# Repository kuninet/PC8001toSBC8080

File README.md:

# PC-8001 50Pバスと、SBC8080バスの変換

## 概要

* PC-8001外部CPUバスをSBC8080バスへ変換するボード

## 必要な電子部品等...

* 74LS32 OR GATE
* 74LS05 NOT (OPENドレイン)

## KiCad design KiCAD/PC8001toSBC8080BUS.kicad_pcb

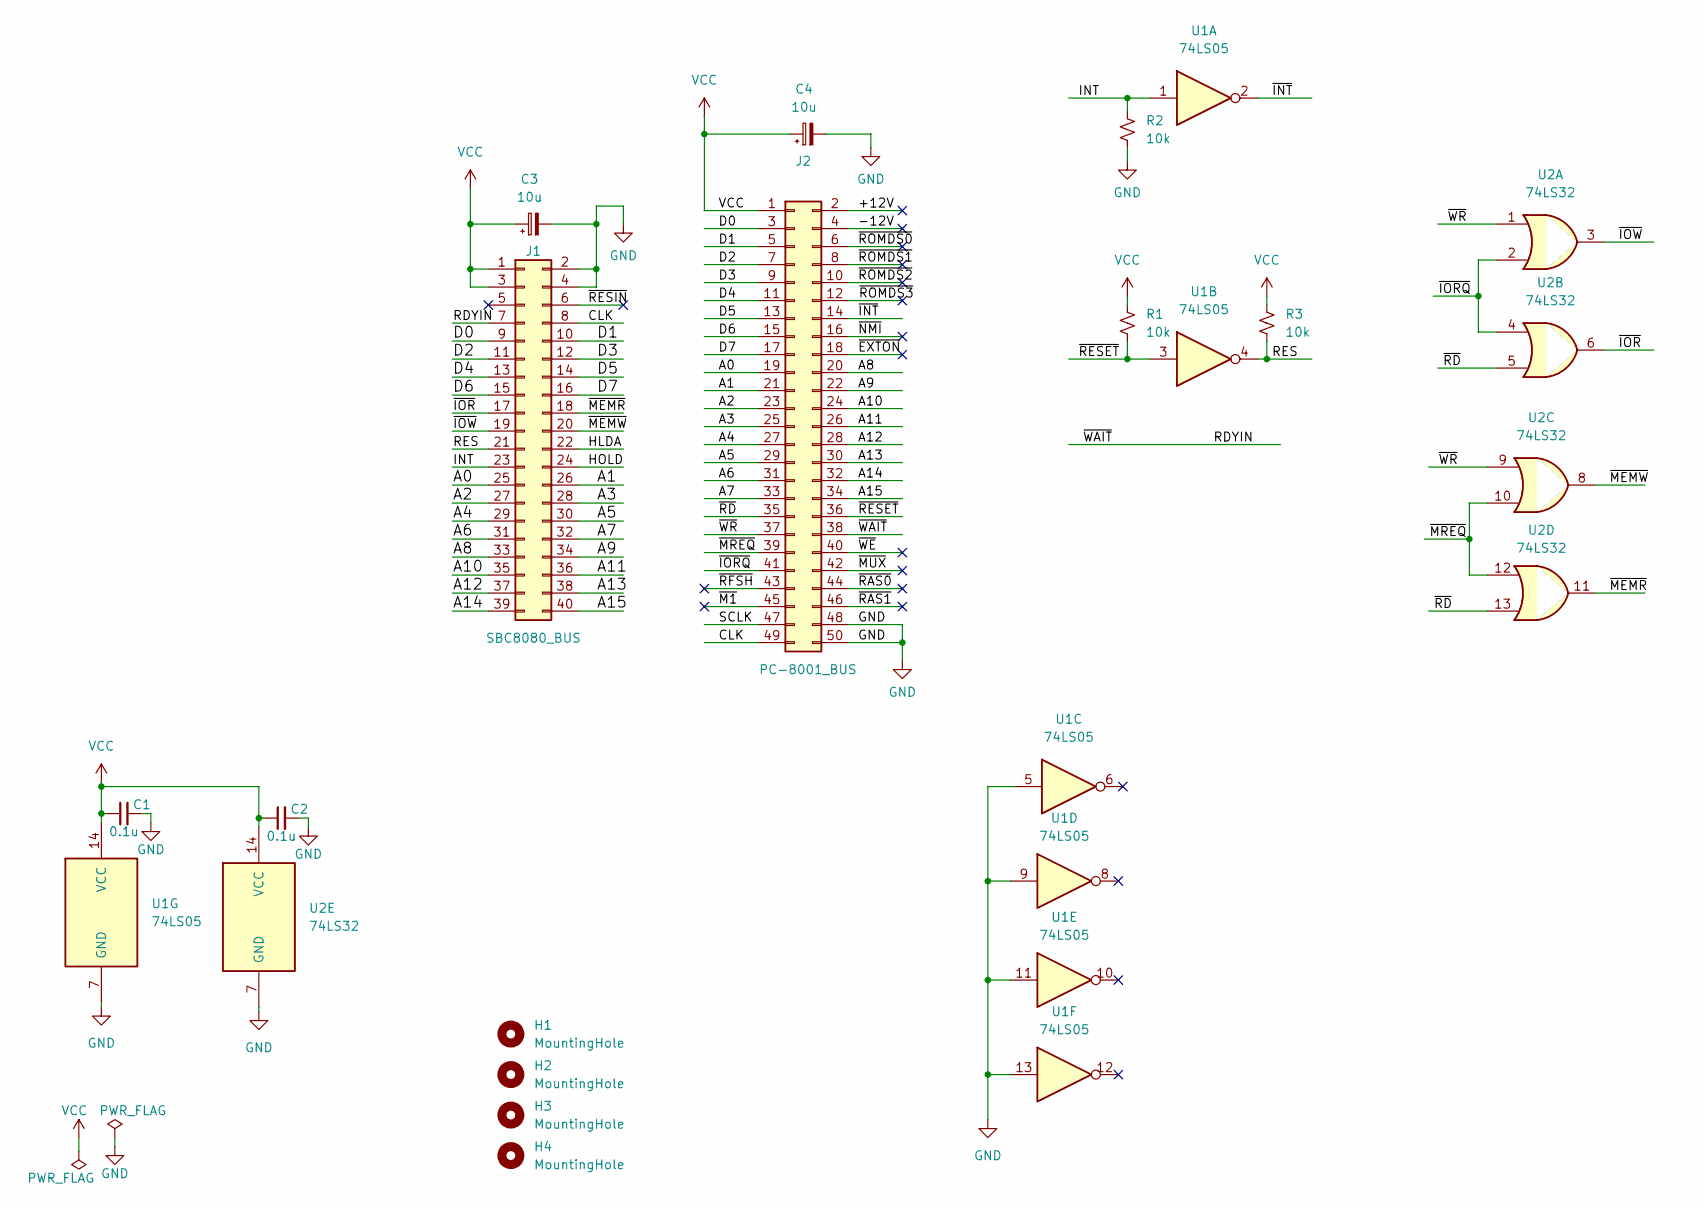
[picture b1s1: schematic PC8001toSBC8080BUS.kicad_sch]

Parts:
C1, C2: 0.1u
C3, C4: 10u
H1, H2, H3, H4: MountingHole
J1: SBC8080_BUS
J2: PC-8001_BUS
R1, R2, R3: 10k
U1: 74LS05
U2: 74LS32

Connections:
/+12V: J2.2
/-12V: J2.4
/A0: J1.25, J2.19
/A1: J1.26, J2.21
/A2: J1.27, J2.23
/A3: J1.28, J2.25
/A4: J1.29, J2.27
/A5: J1.30, J2.29
/A6: J1.31, J2.31
/A7: J1.32, J2.33
/A8: J1.33, J2.20
/A9: J1.34, J2.22
/A10: J1.35, J2.24
/A11: J1.36, J2.26
/A12: J1.37, J2.28
/A13: J1.38, J2.30
/A14: J1.39, J2.32
/A15: J1.40, J2.34
/CLK: J1.8, J2.49
/D0: J1.9, J2.3
/D1: J1.10, J2.5
/D2: J1.11, J2.7
/D3: J1.12, J2.9
/D4: J1.13, J2.11
/D5: J1.14, J2.13
/D6: J1.15, J2.15
/D7: J1.16, J2.17
/HLDA: J1.22
/HOLD: J1.24
/INT: J1.23, R2.1, U1.1
/RDYIN: J1.7, J2.38
/RES: J1.21, R3.2, U1.4
/SCLK: J2.47
/~EXTON: J2.18
/~INT: J2.14, U1.2
/~IORQ: J2.41, U2.2, U2.4
/~IOR: J1.17, U2.6
/~IOW: J1.19, U2.3
/~M1: J2.45
/~MEMR: J1.18, U2.11
/~MEMW: J1.20, U2.8
/~MREQ: J2.39, U2.10, U2.12
/~MUX: J2.42
/~NMI: J2.16
/~RAS0: J2.44
/~RAS1: J2.46
/~RD: J2.35, U2.5, U2.13
/~RESET: J2.36, R1.2, U1.3
/~RESIN: J1.6
/~RFSH: J2.43
/~ROMDS0: J2.6
/~ROMDS1: J2.8
/~ROMDS2: J2.10
/~ROMDS3: J2.12
/~WE: J2.40
/~WR: J2.37, U2.1, U2.9
GND: C1.2, C2.2, C3.2, C4.2, J1.2, J1.4, J2.48, J2.50, R2.2, U1.5, U1.7 (GND), U1.9, U1.11, U1.13, U2.7 (GND)
VCC: C1.1, C2.1, C3.1, C4.1, J1.1, J1.3, J2.1, R1.1, R3.1, U1.14 (VCC), U2.14 (VCC)

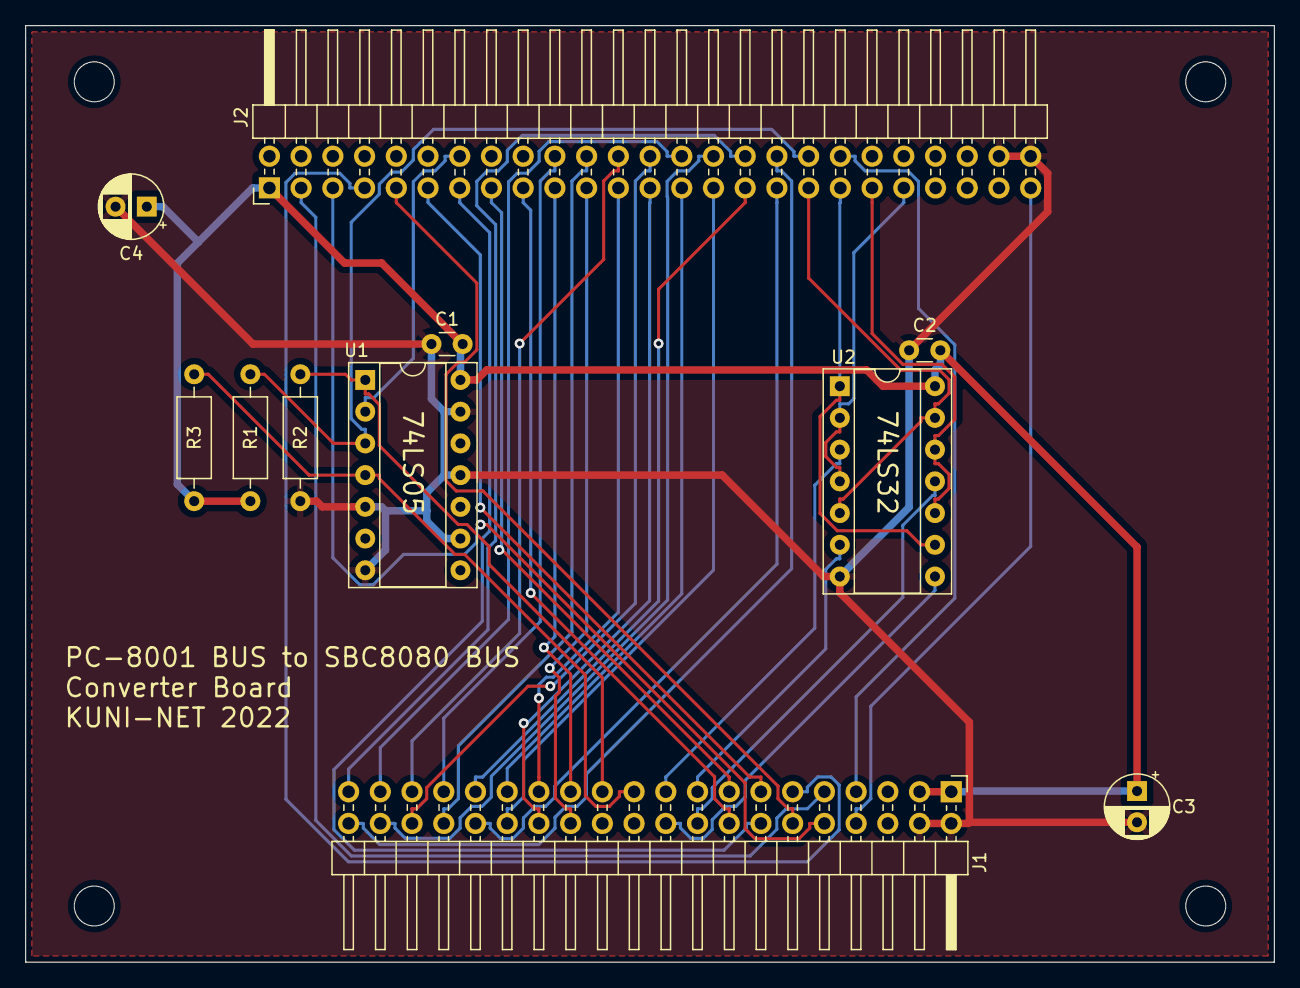
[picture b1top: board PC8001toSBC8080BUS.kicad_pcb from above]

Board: 2 copper layers, 100.0 x 75.0 mm, 15 parts (0 on the bottom side), 40 nets.
